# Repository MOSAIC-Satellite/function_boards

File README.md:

# function_boards
This repository contains files for all custom made function boards for MOSAIC as well as a template to make your own.

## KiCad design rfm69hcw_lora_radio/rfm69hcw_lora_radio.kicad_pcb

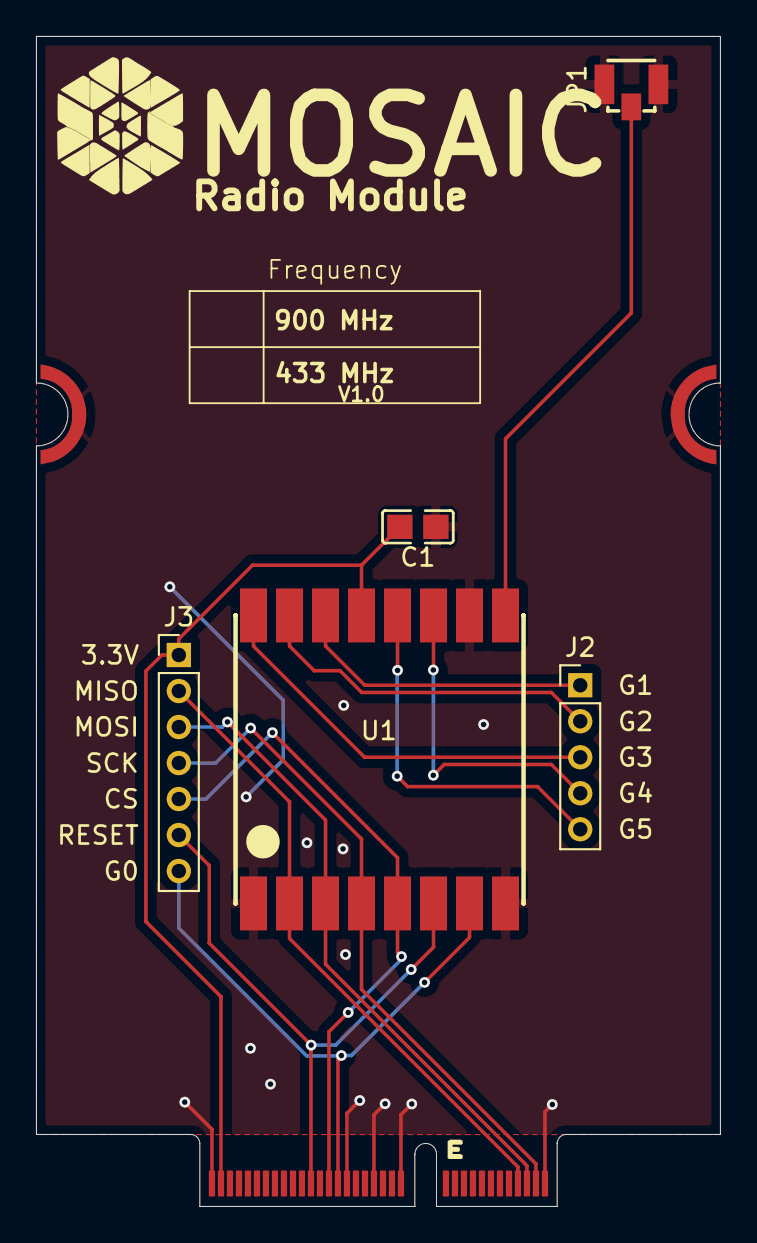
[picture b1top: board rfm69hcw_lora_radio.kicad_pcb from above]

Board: 2 copper layers, 38.0 x 65.0 mm, 6 parts (0 on the bottom side), 14 nets.

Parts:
C1: 10uF; C0805
J1: M.2-CARD-E-22_FUNCTION_STANDARD
J2: Conn_01x05; PinHeader_1x05_P2.00mm_Vertical
J3: Conn_01x07; PinHeader_1x07_P2.00mm_Vertical
JP1: 6GHz; ANT-SMD_UFL-R-SMT-1-10
U1: WIRELM-SMD_RFM69HCW-915S2R

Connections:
+3.3V: C1.2, J1.73 (3.3V), J3.1, U1.13 (3.3V)
/CS: J1.49 (G1/~CS), J3.5, U1.5 (NSS)
/DIO0: J2.1, U1.14 (DIO0)
/DIO1: J2.2, U1.15 (DIO1)
/DIO2: J2.3, U1.16 (DIO2)
/DIO3: J2.4, U1.11 (DIO3)
/DIO4: J2.5, U1.12 (DIO4)
/G0 (IRQ): J1.47 (G0/~INT), J3.7, U1.7 (DIO5)
/MISO (CIPO): J1.7 (SPI_SDO), J3.2, U1.2 (MISO)
/MOSI (COPI): J1.5 (SPI_SDI), J3.3, U1.3 (MOSI)
/RST: J1.53 (G3), J3.6, U1.6 (RESET)
/SCK: J1.3 (SPI_SCK), J3.4, U1.4 (SCK)
GND: C1.1, J1.1 (GND), J1.33 (GND), J1.39 (GND), J1.45 (GND), J1.75 (GND), J1.76 (GND), J1.77 (GND), J1.79 (GND), JP1.1 (GND), JP1.3 (GND), U1.1 (GND), U1.8 (GND), U1.10 (GND)
unnamed: JP1.2 (SIN), U1.9 (ANT)

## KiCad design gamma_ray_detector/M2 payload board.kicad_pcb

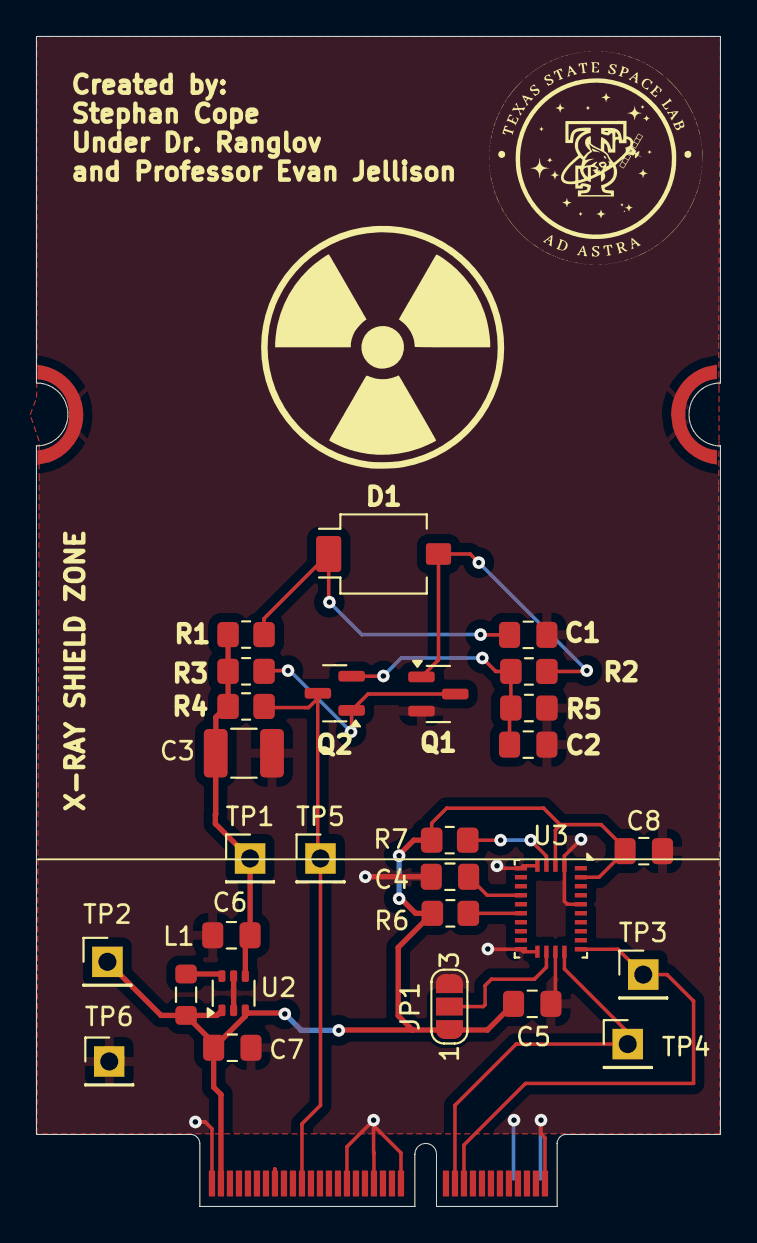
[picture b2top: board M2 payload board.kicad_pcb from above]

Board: 2 copper layers, 38.0 x 65.0 mm, 29 parts (0 on the bottom side), 15 nets.

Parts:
C1, C8: 100nF; C_0805_2012Metric_Pad1.18x1.45mm_HandSolder
C2, C6: 10uF; C_0805_2012Metric_Pad1.18x1.45mm_HandSolder
C3: 100uF; C_1210_3225Metric_Pad1.33x2.70mm_HandSolder
C4, C7: 1uF; C_0805_2012Metric_Pad1.18x1.45mm_HandSolder
C5: 120nF; C_0805_2012Metric_Pad1.18x1.45mm_HandSolder
D1: BPW34-SMD; Osram_BPW34S-SMD
J2: CONN E; M.2-CARD-E-22_FUNCTION_STANDARD
JP1: SolderJumper_3_Open; SolderJumper-3_P1.3mm_Open_RoundedPad1.0x1.5mm_NumberLabels
L1: 10uH; L_0805_2012Metric_Pad1.05x1.20mm_HandSolder
Q1, Q2: BC849; SOT-23
R1, R3: 220k; R_0805_2012Metric_Pad1.20x1.40mm_HandSolder
R2: 2.2M; R_0805_2012Metric_Pad1.20x1.40mm_HandSolder
R4: 4.7k; R_0805_2012Metric_Pad1.20x1.40mm_HandSolder
R5: 1k; R_0805_2012Metric_Pad1.20x1.40mm_HandSolder
R6, R7: 10k; R_0805_2012Metric_Pad1.20x1.40mm_HandSolder
TP1, TP2, TP3, TP4, TP5, TP6: TestPoint; PinHeader_1x01_P2.54mm_Vertical
U2: LTC3525-5; SOT-363_SC-70-6
U3: BNO055; LGA-28_5.2x3.8mm_P0.5mm

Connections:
3.3V: C5.1, C7.2, C8.1, J2.73 (3.3V), JP1.1 (A), L1.1, R6.1, R7.1, TP2.1, U2.1 (~SHDN), U2.3 (VIN), U3.3 (VDD), U3.28 (VDDIO)
+5V: C3.1, C6.2, R1.1, R3.2, R4.1, TP1.1, U2.4 (VOUT)
/NBOOT: R7.2, U3.4 (~BOOT_LOAD_PIN)
/NRST: R6.2, U3.11 (~RESET)
AnalogOut1: J2.55 (F4), Q2.3 (C), R4.2, TP5.1
GND: C1.2, C2.1, C3.2, C4.1, C5.2, C6.1, C7.1, C8.2, J2.1 (GND), J2.2 (GND), J2.8 (GND), J2.33 (GND), J2.39 (GND), J2.45 (GND), J2.75 (GND), JP1.3 (B), Q1.2 (E), R5.2, TP6.1, U2.2 (GND), U2.5 (GND), U3.2 (GND), U3.5 (PS1), U3.6 (PS0), U3.15 (GNDIO), U3.16 (GNDIO), U3.18 (COM2), U3.25 (GNDIO)
unnamed: D1.2 (A), Q1.1 (B), R2.1
unnamed: C1.1, D1.1 (K), R1.2
unnamed: JP1.2 (C), U3.17 (COM3)
unnamed: Q1.3 (C), Q2.1 (B), R3.1
unnamed: C2.2, Q2.2 (E), R2.2, R5.1
unnamed: L1.2, U2.6 (SW)
unnamed: C4.2, U3.9 (CAP)
SCL: J2.21 (I2C_SCL), TP4.1, U3.19 (COM1)
SDA: J2.19 (I2C_SDA), TP3.1, U3.20 (COM0)

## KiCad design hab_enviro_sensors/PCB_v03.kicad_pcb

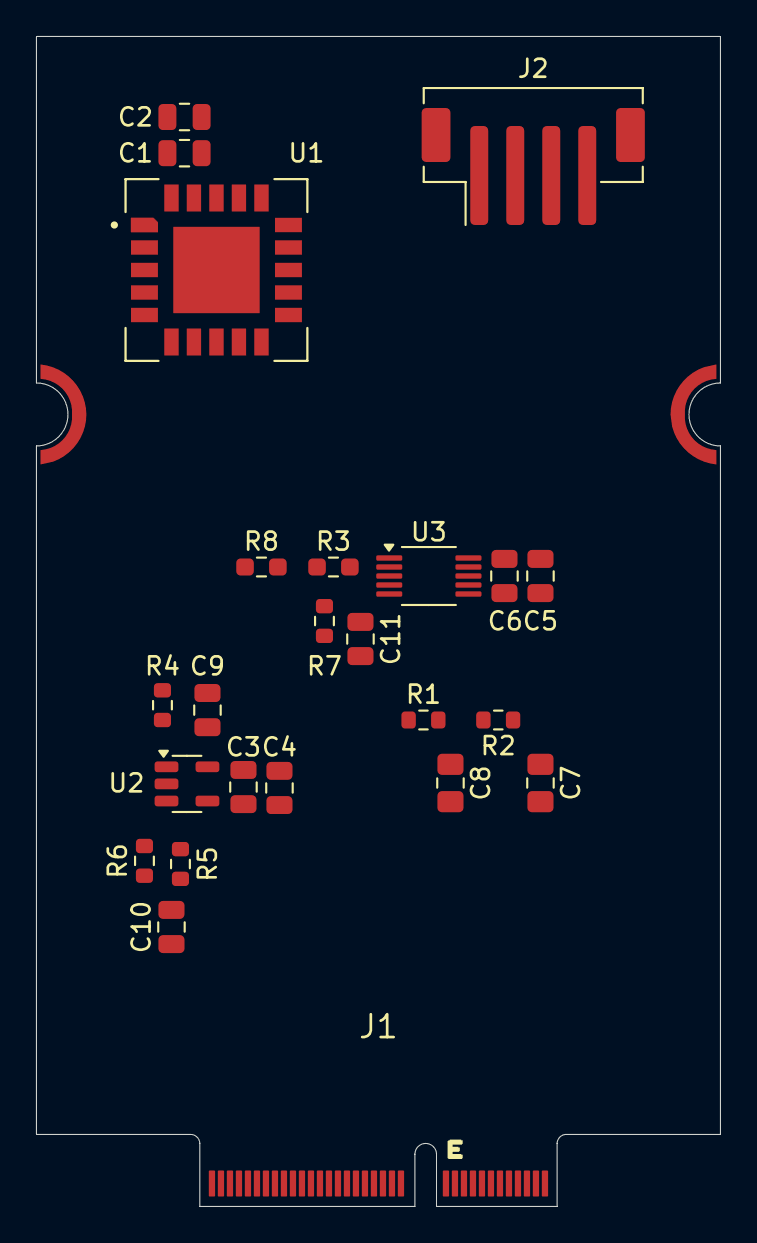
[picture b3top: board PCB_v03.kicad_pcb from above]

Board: 2 copper layers, 38.0 x 65.0 mm, 24 parts (0 on the bottom side), 12 nets, no tracks yet.

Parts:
C1, C3, C5, C10: 0.1u; C_0805_2012Metric
C2, C4, C6: 1u; C_0805_2012Metric
C7, C8: 1u; C_0805_2012Metric_Pad1.18x1.45mm_HandSolder
C9: 220p; C_0805_2012Metric
C11: 2.2n; C_0805_2012Metric
J1: M.2-CARD-E-22_FUNCTION_STANDARD
J2: Conn_01x04; JST_PH_B4B-PH-SM4-TB_1x04-1MP_P2.00mm_Vertical
R1, R2: 1k; R_0603_1608Metric
R3, R8: 10k; R_0603_1608Metric_Pad0.98x0.95mm_HandSolder
R4: 1M; R_0603_1608Metric
R5, R6: 10k; R_0603_1608Metric
R7: 100; R_0603_1608Metric
U1: SCD41-D-R2; XDCR_SCD41-D-R2
U2: OPA320AIDBVR; SOT-23-5
U3: ADS1115IDGSR; VSSOP-10_3x3mm_P0.5mm

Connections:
+3.3V: C1.1, C2.1, C3.1, C4.1, C5.1, C6.1, J1.73 (3.3V), J2.3, R3.1, R5.1, R6.1, R8.2, U1.7 (VDD), U1.19 (VDDH), U2.5 (V+), U3.8 (VDD)
GND: C1.2, C2.2, C3.2, C4.2, C5.2, C6.2, C7.2, C8.2, C9.2, C10.2, C11.2, J1.1 (GND), J1.33 (GND), J1.39 (GND), J1.45 (GND), J1.75 (GND), J1.76 (GND), J1.77 (GND), J1.79 (GND), J2.1, J2.4, R4.2, R5.2, R8.1, U1.6 (GND), U1.20 (GND), U1.21 (GND), U2.2 (V-), U3.1 (ADDR), U3.3 (GND), U3.5 (AIN1), U3.6 (AIN2), U3.7 (AIN3)
I2C_SCL: J1.21 (I2C_SCL), U1.9 (SCL), U3.10 (SCL)
I2C_SDA: J1.19 (I2C_SDA), U1.10 (SDA), U3.9 (SDA)
LPF-OUT: C8.1, R2.2, R7.1
unnamed: C7.1, R1.2, R2.1
unnamed: J1.72 (VCC), J1.74 (VCC)
unnamed: C10.1, R6.2, U2.3 (+IN)
unnamed: C11.1, R7.2, U3.4 (AIN0)
unnamed: R3.2, U3.2 (ALERT/RDY)
OPA320-IN: C9.1, J2.2, R4.1, U2.4 (-IN)
OPA320-OUT: R1.1, U2.1 (OUT)

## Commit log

2025-09-19 Added initial files
2026-01-04 Added new modules
2026-03-19 New Radio Board
    Added a new LoRa radio function board
